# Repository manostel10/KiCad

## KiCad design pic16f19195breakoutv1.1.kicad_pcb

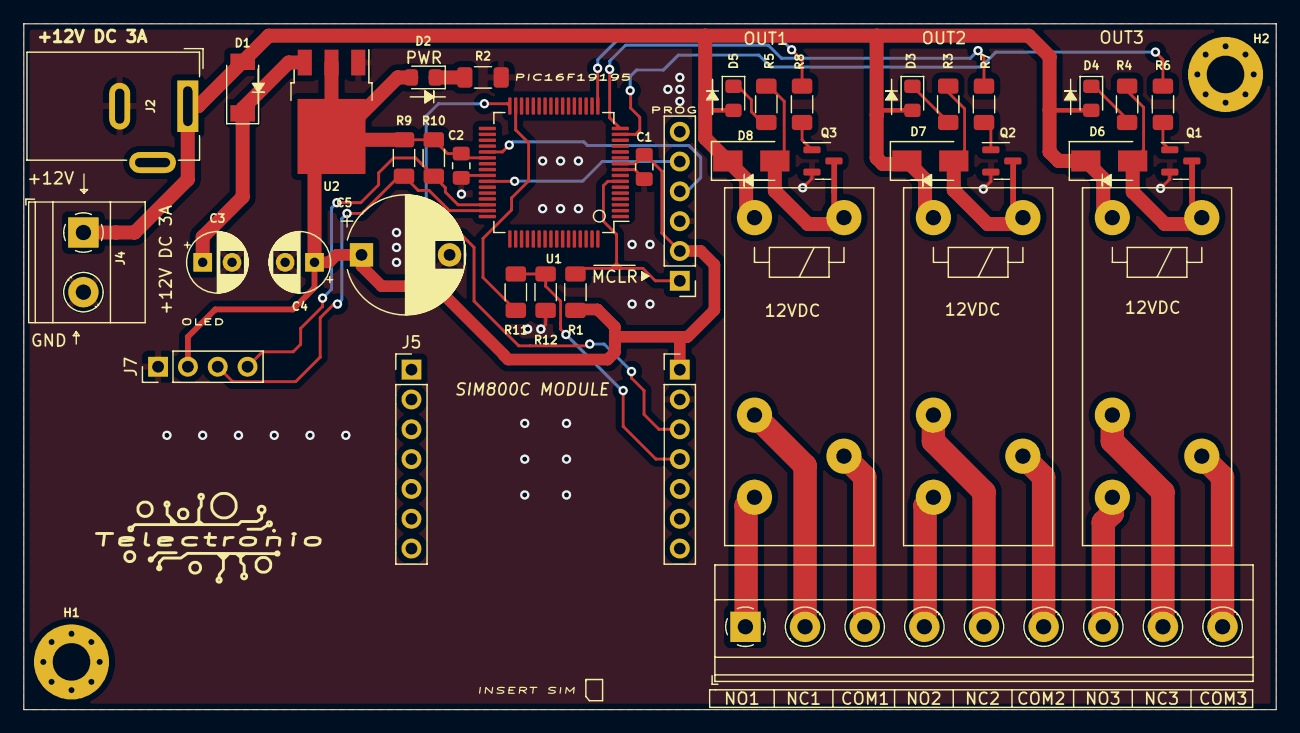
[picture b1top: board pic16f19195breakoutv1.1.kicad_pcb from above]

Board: 2 copper layers, 106.7 x 58.4 mm, 42 parts (0 on the bottom side), 34 nets.

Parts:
C1, C2: 100n; C_0805_2012Metric_Pad1.18x1.45mm_HandSolder
C3, C4: 10uF/25V; CP_Radial_D5.0mm_P2.50mm
C5: 1000uF; CP_Radial_D10.0mm_P7.50mm
D1: BAT54J; D_SOD-128
D2: PWR; LED_0805_2012Metric_Pad1.15x1.40mm_HandSolder
D3: LED2; LED_0805_2012Metric_Pad1.15x1.40mm_HandSolder
D4: LED3; LED_0805_2012Metric_Pad1.15x1.40mm_HandSolder
D5: LED1; LED_0805_2012Metric_Pad1.15x1.40mm_HandSolder
D6, D7, D8: US1M; D_SMA
H1, H2: MountingHole; MountingHole_3.2mm_M3_Pad_Via
J1: PROG PINS; PinHeader_1x06_P2.54mm_Vertical
J2: Barrel_Jack_MountingPin; BarrelJack_Wuerth_6941xx301002
J3: RELAY OUTPUTS; TerminalBlock_Phoenix_MKDS-1,5-9-5.08_1x09_P5.08mm_Horizont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
J4: +12V DC; TerminalBlock_Phoenix_MKDS-1,5-2-5.08_1x02_P5.08mm_Horizont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
J5: SIM800C LEFT; PinHeader_1x07_P2.54mm_Vertical
J6: SIM800C RIGHT; PinHeader_1x07_P2.54mm_Vertical
J7: OLED; PinHeader_1x04_P2.54mm_Vertical
Q1, Q2, Q3: BC847; SOT-23
R1, R9, R10: 10k; R_1206_3216Metric_Pad1.30x1.75mm_HandSolder
R2, R6, R7, R8: 330; R_1206_3216Metric_Pad1.30x1.75mm_HandSolder
R3, R4, R5: 1k; R_1206_3216Metric_Pad1.30x1.75mm_HandSolder
R11: 5K; R_1206_3216Metric_Pad1.30x1.75mm_HandSolder
R12: 10K; R_1206_3216Metric_Pad1.30x1.75mm_HandSolder
RL1, RL2, RL3: G2RL-2-DC12; Relay_SPDT_Schrack-RT1-FormC_RM3.5mm
U1: PIC16F19195; TQFP-64_10x10mm_P0.5mm
U2: NCP1117-5.0_TO252; TO-252-3_TabPin2

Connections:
5VREG: C1.1, C2.1, C4.1, C5.1, D2.2 (A), J1.2, J6.1, J7.2, R1.1, R9.1, R10.1, U1.10 (VDD), U1.38 (VDD), U2.2 (VO)
COM1: J3.3, RL3.11
COM2: J3.6, RL2.11
COM3: J3.9, RL1.11
DC_IN: D1.2 (A), D3.2 (A), D4.2 (A), D5.2 (A), D6.1 (K), D7.1 (K), D8.1 (K), J2.1, J4.1, RL1.A2, RL2.A2, RL3.A2
GND: C1.2, C2.2, C3.2, C4.2, C5.2, J1.3, J2.2, J4.2, J6.2, J7.1, Q1.2 (E), Q2.2 (E), Q3.2 (E), R2.2, R12.1, U1.9 (VSS), U1.41 (VSS), U2.1 (GND)
I2C_SCL: J7.3, R9.2, U1.47 (RB1/SEG8)
I2C_SDATA: J7.4, R10.2, U1.46 (RB2/SEG9)
ICSPCLK: J1.5, U1.42 (RB6/SEG38/ICSPCLK)
ICSPDAT: J1.4, U1.37 (RB7/SEG39/ICSPDAT)
MCLR: J1.1, R1.2, U1.7 (VPP/~MCLR/RG5)
NC1: J3.2, RL3.12
NC2: J3.5, RL2.12
NC3: J3.8, RL1.12
NO1: J3.1, RL3.14
NO2: J3.4, RL2.14
NO3: J3.7, RL1.14
unnamed: C3.1, D1.1 (K), U2.3 (VI)
unnamed: D2.1 (K), R2.1
unnamed: D3.1 (K), R3.1
unnamed: D4.1 (K), R4.1
unnamed: D5.1 (K), R5.1
unnamed: D6.2 (A), Q1.3 (C), R4.2, RL1.A1
unnamed: D7.2 (A), Q2.3 (C), R3.2, RL2.A1
unnamed: D8.2 (A), Q3.3 (C), R5.2, RL3.A1
unnamed: Q1.1 (B), R6.1
unnamed: Q2.1 (B), R7.1
unnamed: Q3.1 (B), R8.1
unnamed: R11.2, U1.31 (RC6/SEG27)
OUT1: R8.2, U1.17 (SEG19/RF1)
OUT2: R7.2, U1.16 (SEG20/RF2)
OUT3: R6.2, U1.15 (SEG21/RF3)
RX1: J6.3, U1.32 (RC7/SEG28)
TX3.3V: J6.4, R11.1, R12.2
